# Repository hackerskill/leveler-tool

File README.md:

# leveler-tool
&#x09;

### A interactive leveler tool based on rp 2040 with acceleration sensor and led matrix.
---
Used to measure angle of displacement for a horizontal or a vertical surface, based on RP2040 with acceleration sensor and led matrix. Modules plug in into the custom PCB, allowing for measuring angle of displacement for a horizontal or a vertical surface.

## Features
- XIAO RP2040 acts as the main microcontroller
- Real time tilt measurement using an ADXL345
- MAX7219 LED matrix for visual feedback
- Active buzzer for audio feedback
- Cherry MX switch for user input
- USB-C connectivity through the XIAO RP2040 for Power
- Compact custom PCB

---

# Schematics-

# PCB-

## How It Works

1. The ADXL345 continuously measures acceleration along its three axes.

2. The RP2040 processes these measurements and converts them to angle. The resulting angle is used to determine which leds should be turned on using the LED matrix.

3. The Buzzer turns on when the device is exactly parallel to the surface.

4. The Cherry MX switch is used for user interaction such as changing modes or temporary turning off.

# BOM-
| Component Name | Description | Quantity |
| :--- | :--- | :---: |
| **Seeed Studio Xiao RP2040** | Devboard for RP2040 Chipset | 1 |
| **MAX7219** | 8x8 LED Display Matrix | 1 |
| **ADXL345** | 3-Axis Digital Accelerometer Module | 1 |
| **Active Buzzer** | 3V3 Active Buzzer | 1 |
| **Custom PCB** | Custom PCB | 1 |

---

**Made by hackerskill**

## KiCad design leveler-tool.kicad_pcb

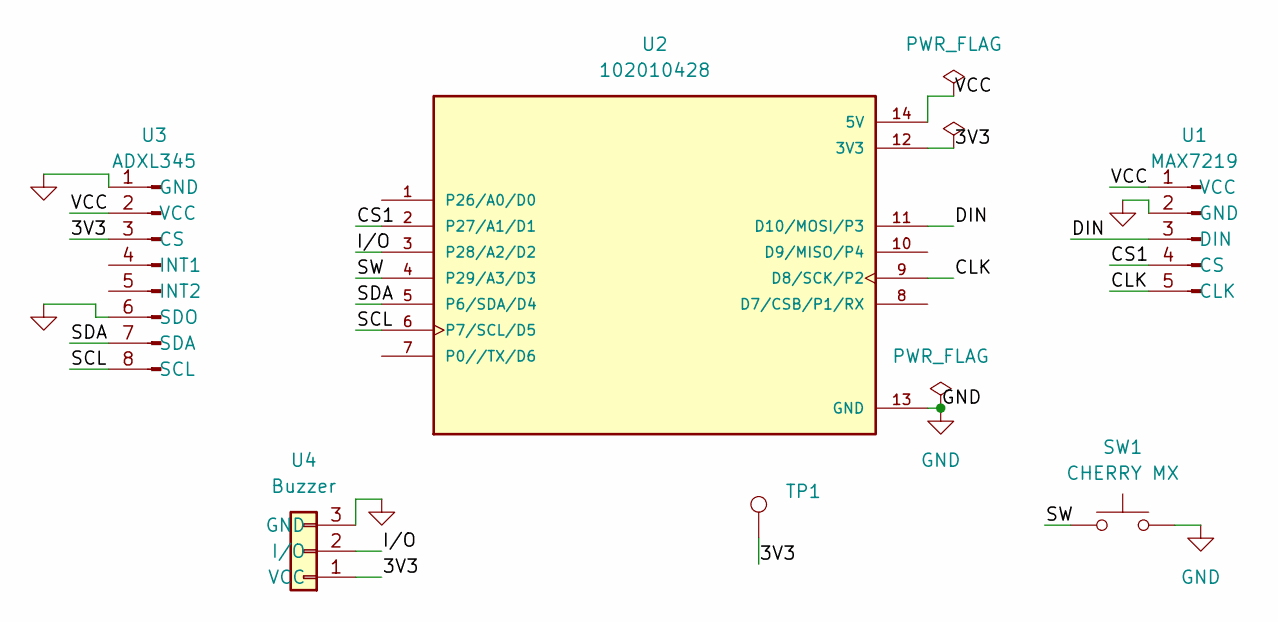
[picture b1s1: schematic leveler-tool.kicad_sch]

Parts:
SW1: CHERRY MX; SW_Cherry_MX_1.00u_PCB
TP1: TestPoint; PinSocket_1x01_P2.54mm_Vertical
U1: MAX7219; PinSocket_1x05_P2.54mm_Vertical
U2: 102010428; XIAO-RP2040-DIP; PARTREV 1.3
U3: ADXL345; PinSocket_1x08_P2.54mm_Vertical
U4: Buzzer; PinSocket_1x03_P2.54mm_Vertical

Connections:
/3V3: TP1.1 (1_1), U2.12 (3V3), U3.3 (CS), U4.1 (VCC)
/CLK: U1.5 (CLK), U2.9 (D8/SCK/P2)
/CS1: U1.4 (CS), U2.2 (P27/A1/D1)
/DIN: U1.3 (DIN), U2.11 (D10/MOSI/P3)
/I/O: U2.3 (P28/A2/D2), U4.2 (I/O)
/SCL: U2.6 (P7/SCL/D5), U3.8 (SCL)
/SDA: U2.5 (P6/SDA/D4), U3.7 (SDA)
/SW: SW1.1, U2.4 (P29/A3/D3)
/VCC: U1.1 (VCC), U2.14 (5V), U3.2 (VCC)
GND: SW1.2, U1.2 (GND), U2.13 (GND), U3.1 (GND), U3.6 (SDO), U4.3 (GND)

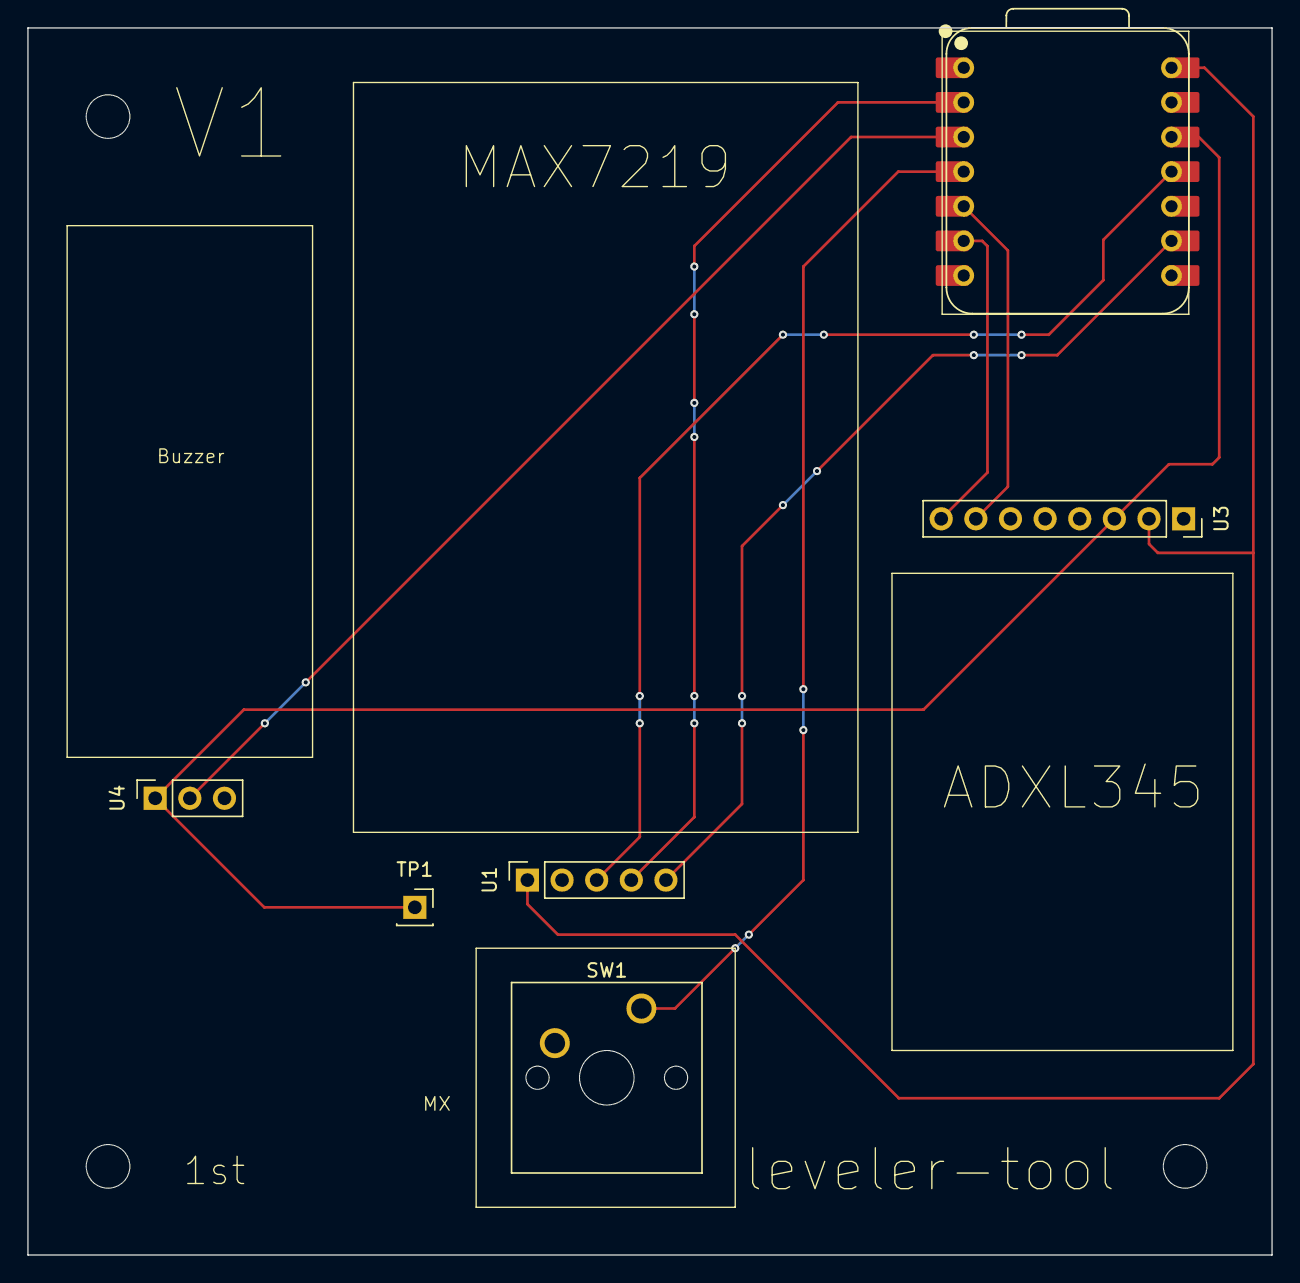
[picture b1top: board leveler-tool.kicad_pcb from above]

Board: 2 copper layers, 91.2 x 90.0 mm, 6 parts (0 on the bottom side), 10 nets.
